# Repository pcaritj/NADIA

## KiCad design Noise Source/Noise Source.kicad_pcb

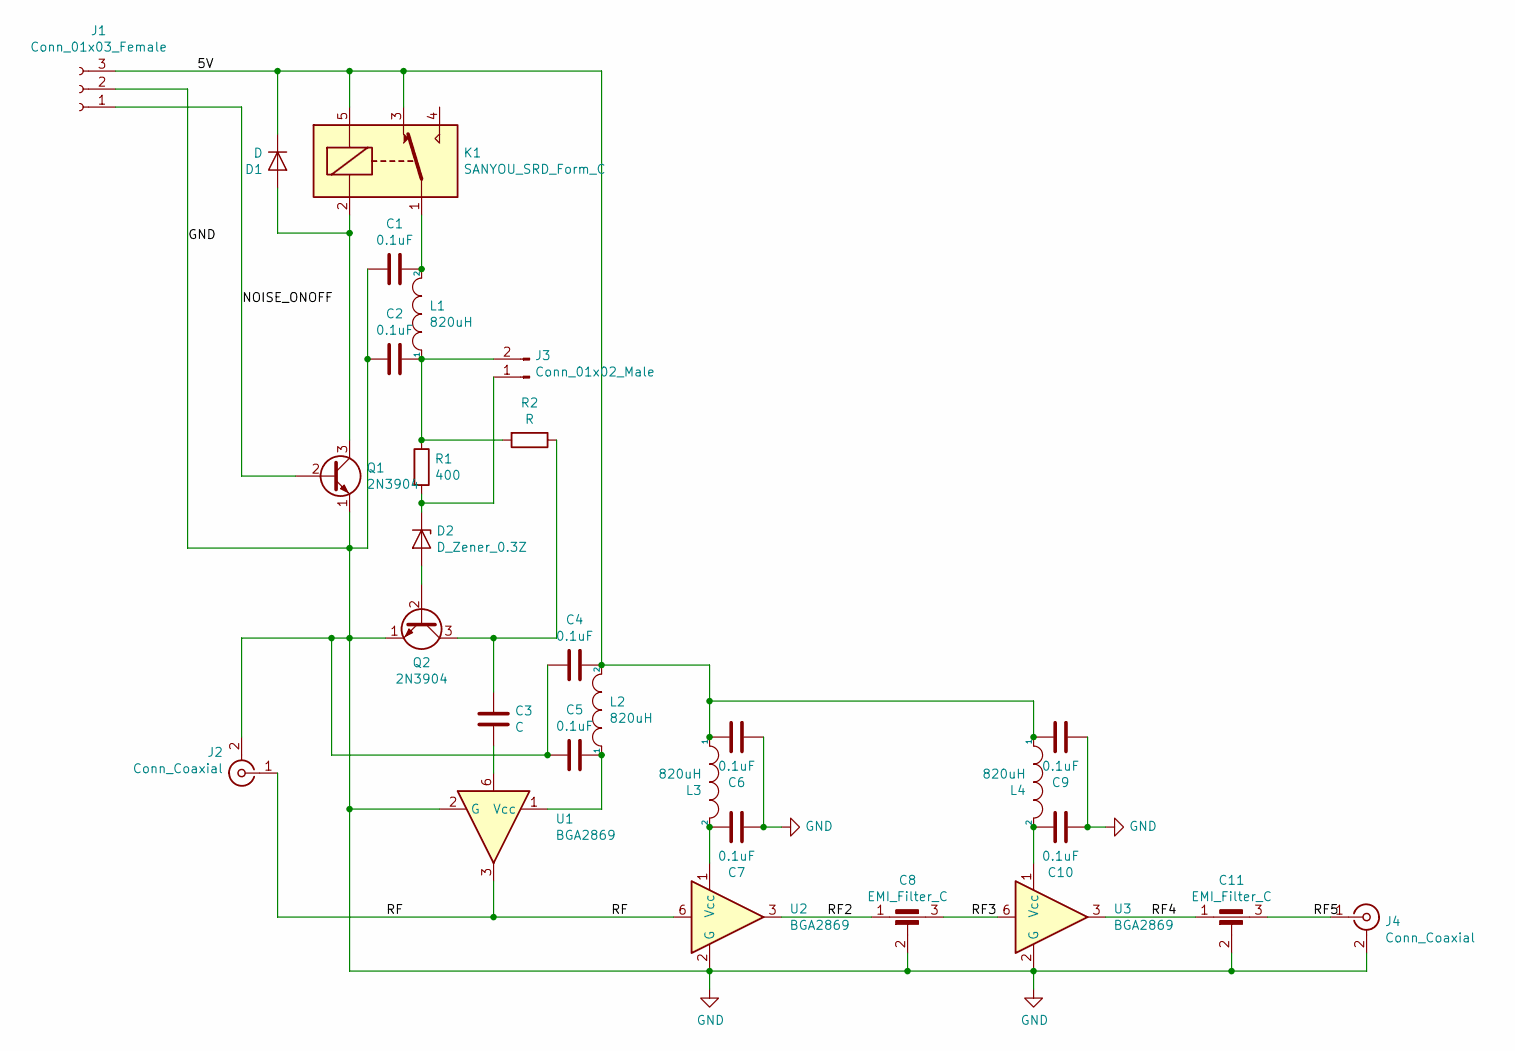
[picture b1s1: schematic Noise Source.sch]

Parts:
C1, C2, C4, C5, C6, C7, C9, C10: 0.1uF; C_0805_2012Metric_Pad1.15x1.40mm_HandSolder
C3: C; C_0805_2012Metric_Pad1.15x1.40mm_HandSolder
C8, C11: EMI_Filter_C; 1210_GND_PAD
D1: D; D_SOD-323
D2: D_Zener_0.3Z; D_SOD-123
J1: Conn_01x03_Female; JST_ZE_SM03B-ZESS-TBT_1x03-1MP_P1.50mm_Horizontal
J2, J4: Conn_Coaxial; SMA_Amphenol_132289_EdgeMount
J3: Conn_01x02_Male; PinHeader_1x02_P2.54mm_Vertical
K1: SANYOU_SRD_Form_C; Relay_SPDT_SANYOU_SRD_Series_Form_C
L1, L2, L3, L4: 820uH; L_1812_4532Metric_Pad1.30x3.40mm_HandSolder
Q1, Q2: 2N3904; SC-59_Handsoldering
R1: 400; R_0805_2012Metric_Pad1.15x1.40mm_HandSolder
R2: R; R_0805_2012Metric_Pad1.15x1.40mm_HandSolder
U1, U2, U3: BGA2869; SOT-363_SC-70-6

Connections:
/5V: C4.1, C6.1, C9.1, D1.1 (K), J1.3, K1.3, K1.5, L2.2, L3.1, L4.1
/NOISE_ONOFF: J1.1, Q1.2 (B)
/RF: J2.1 (In), U1.3, U2.6
/RF2: C8.1, U2.3
/RF3: C8.3, U3.6
/RF4: C11.1, U3.3
/RF5: C11.3, J4.1 (In)
GND: C1.2, C2.2, C4.2, C5.2, C6.2, C7.2, C8.2, C9.2, C10.2, C11.2, J1.2, J2.2 (Ext), J4.2 (Ext), Q1.1 (E), Q2.1 (E), U1.2 (G), U1.4 (G), U1.5 (G), U2.2 (G), U2.4 (G), U2.5 (G), U3.2 (G), U3.4 (G), U3.5 (G)
unnamed: C1.1, K1.1, L1.2
unnamed: C2.1, J3.2, L1.1, R1.1, R2.2
unnamed: C3.1, Q2.3 (C), R2.1
unnamed: C3.2, U1.6
unnamed: C5.1, L2.1, U1.1 (Vcc)
unnamed: C7.1, L3.2, U2.1 (Vcc)
unnamed: C10.1, L4.2, U3.1 (Vcc)
unnamed: D1.2 (A), K1.2, Q1.3 (C)
unnamed: D2.1 (K), J3.1, R1.2
unnamed: D2.2 (A), Q2.2 (B)

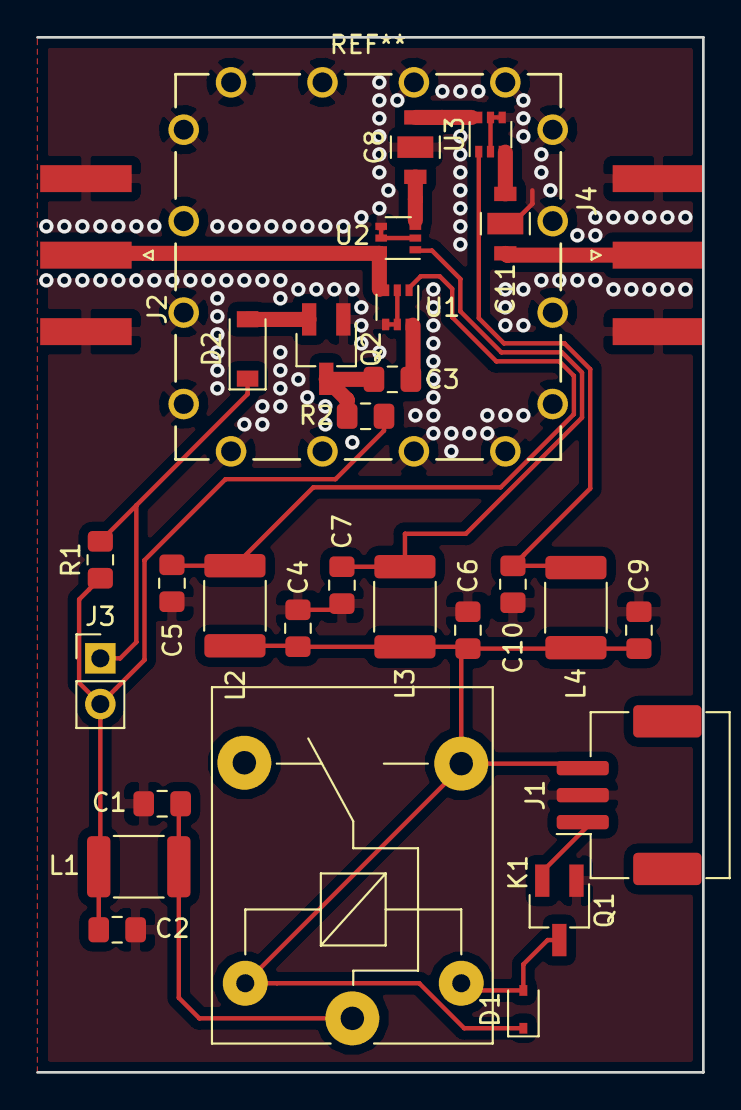
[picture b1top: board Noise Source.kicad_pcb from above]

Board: 2 copper layers, 37.0 x 57.5 mm, 29 parts (0 on the bottom side), 18 nets.

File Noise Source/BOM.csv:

Id,Designator,Package,Quantity,Designation,Supplier and ref
1,REF**,Wuerth_36503205_20x20mm,1,Wuerth_36503205_20x20mm,732-11659-ND
2,"C4,C1,C2,C5,C6,C7,C9,C10",C_0805_2012Metric_Pad1.15x1.40mm_HandSolder,8,0.1uF,478-11911-1-ND
3,C3,C_0805_2012Metric_Pad1.15x1.40mm_HandSolder,1,C,478-11911-1-ND
4,"C8,C11",1210_GND_PAD,2,EMI_Filter_C,1292-1110-1-ND
5,D1,D_SOD-323,1,D,NSR0530HT1GOSCT-ND
6,D2,D_SOD-123,1,D_Zener_0.3Z,MM3Z3V3BTR-ND
7,J1,JST_ZE_SM03B-ZESS-TBT_1x03-1MP_P1.50mm_Horizontal,1,Conn_01x03_Female,455-2396-6-ND
8,"J2,J4",SMA_Amphenol_132289_EdgeMount,2,Conn_Coaxial,CON-SMA-EDGE-S-ND
9,J3,PinHeader_1x02_P2.54mm_Vertical,1,Conn_01x02_Male,
10,K1,Relay_SPDT_SANYOU_SRD_Series_Form_C,1,SANYOU_SRD_Form_C,
11,"L1,L2,L3,L4",L_1812_4532Metric_Pad1.30x3.40mm_HandSolder,4,820uH,495-1984-2-ND
12,"Q1,Q2",SC-59_Handsoldering,2,2N3904,1727-2919-1-ND
13,R1,R_0805_2012Metric_Pad1.15x1.40mm_HandSolder,1,400,YAG4897CT-ND
14,R2,R_0805_2012Metric_Pad1.15x1.40mm_HandSolder,1,R,311-6.04KCRCT-ND
15,"U1,U2,U3",SOT-363_SC-70-6,3,BGA2869,568-8535-1-ND
,,,,JST connector,455-2412-ND

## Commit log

2018-02-04 Implement basic rx streaming.
2018-02-04 Add sftp sync.
2018-02-04 Elimate tqdm dependency.
2018-02-04 Reverse compatibility for Python < 3.6.
2018-02-04 Same.
2018-02-04 Circumvent sftp certificate checking (temporarily).
2018-02-04 Add explicit idna import.
2018-02-04 Correct idna workarounds.
2018-02-04 Set bandwidth; correct measurement interval.
2018-02-11 Beginning of updated analysis software.
2018-02-11 Basic visualization features.
2018-09-30 Added setup.py
2018-09-30 Restructure for use with pip
    Former-commit-id: 0178e16383faf32c3913fe99c53503264cddb77c
2018-09-30 Deleted erroneously uploaded raw data.
    Former-commit-id: 69dbfc6eab4fd09b20c0e67a541de30f4291a2b9
2018-09-30 Moved setup.py
2018-09-30 Added extremely crude autoupdating.
2018-09-30 Updated to make only one observation
2018-09-30 Added diagnostic messages
2018-09-30 Added more diagnostic messages.
2018-09-30 Added second iteration for testing.
2018-09-30 Explicitly terminate SDR streams.
2018-09-30 MOved termination to (hopefully) avoid unexplained segfault.
2018-09-30 Add execution script for supervisorctl
2018-09-30 Corrected path in exec script.
2018-09-30 Updated exec script
2018-09-30 Increased number of observations.
2018-11-05 Replace blank frame with noise diode measurement.
2018-11-05 Add simple script to enumerate devices.
2018-11-05 Update sftp host.
2018-11-05 Reduced default number of observations.
2018-11-05 Correct 'fig' typo.
2018-11-05 Increase upload frequency.
2018-11-07 Upload to s3
2018-11-07 Correct s3 upload code to read in binary mode.
2018-11-07 Debug connection reset error from boto.
2018-11-17 Prototype integrated noise source and receiver chain.
2018-11-27 Added prototype geometric delay analysis.
